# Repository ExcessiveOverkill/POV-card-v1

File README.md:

# Persistence of Vision Badge
Turn on then shake side to side to view the images or animations programmed into the badge.

## Specs:
- Requires 2x CR2032 batteries (badge is not rechargeable)
- Credit card sized: 2.1" x 3.3" (54mm x 84mm)
- 0.8mm PCB thickness, 4mm total thickness with components
- Black PCB soldermask
- 32 bright white leds
- ENIG (thin gold) plated

## Features:
- Image or animation display
- User programmable images/animations over USB-C
- User configurable modes set by tapping the badge
- 4-bit grayscale image support
- Many new display modes
- XYZ Accelerometer
- True power-off (batteries last when not in use)
- Auto power-off

# How to use:
## Turning On:
1. Press "ON" button on badge.
2. Badge will display power-on animation when first powered on.

Pressing the "ON" button once badge is already on will have no effect.

## Turning Off:
1. Do nothing
2. Badge will automatically power off after it is no longer being interacted with for around 20 seconds. It will also power off regardless of interaction after 5 minutes.

## Changing Mode:
1. Turn badge on
2. Tap top of badge downward 3 times quickly to enter the mode menue, it should display the current mode by turning on an LED. The distance the LED is from the bottom of the badge shows what mode it is in.
3. Tap top of badge downward to move LED down, Tap bottom of badge upward to move LED up
4. Wait 3 seconds for badge to enter new mode. You may shake the badge while in the mode menu to view what mode is selected. For SAVE MODE, LEVEL CAL, RESET and USB UPDATE, shaking is also the confirmation (see Mode Verification).
5. Done!

## USB Programming:
1. Turn badge on
2. Plug into a USB-A port on the computer, or into a USB-C to USB-A adapter or hub, using a USB-C to USB-A cable that carries data. A USB-C port on the computer will not work: the badge's connector has no CC pull-down resistors, so a USB-C host never enables the connection.
3. Badge will display slow pulsing to indicate USB connection.
4. Badge should show up as a USB storage device (flash drive).
5. Copy your BMP file to the badge
6. Done!
   
### BMP File Requirements:
- 1-bit or 4-bit grayscale
- 8, 16, or 32 pixels tall
- 128 or less pixels wide (per frame)
- Filename must end in "1" or "2" to indicate which slot you want to program
- For animations (multiple frames displayed in sequence), the filename must start with "SEQ"
- Animation frames must be separated by a 1 pixel wide column of alternating colors (0-1 for 1-bit, 0-15 for 4-bit). With the top pixel starting as 1 or 15 (white).
- File size must be less than 2KB

## How to get a good image
Image quality greatly depends on the shaking motion. Use mode 8: "IMAGE LINE TEST" to visualize your shake motion.
### Things to improve display quality
- Hold badge further away
- Smooth, uniform shaking. Slower and more consistent is better than fast and crazy.
- Shake left/right, not tilted or up/down
- Symmetrical movement, *not* like trying to shake ketchup out of a bottle.

## Modes
### 1. DISPLAY BOTH
Display both the pre-programmed image/animation shipped with the badge as well as all custom user-programmed images/animations.

### 2. DISPLAY CUSTOM
Display only the custom user-programmed images/animations.

### 3. LEVEL
Emulates a bubble level. Hold the badge edge against a vertical or horizontal surface. Use the "LEVEL CAL" mode to improve accuracy.

### 4. BALL SIM
LEDs display a "ball" that reacts to how you move and tilt the badge.

### 5. SAVE MODE
Save the last selected mode and automatically switch to it on the next power-on.
This function requires verification (see below).

### 6. LEVEL CAL
Calibrate the angles the badge uses for "LEVEL" mode. After entering this mode, hold the long badge still against a known horizontal surface until the LEDs all turn on. Then hold the short edge still against the surface until the "bubble" resets to center.
This function requires verification (see below).

### 7. RESET
Clears all user-programmed memory. Badge will power off after this mode is selected.
This function requires verification (see below).

### 8. IMAGE LINE TEST
Displays a diagonal line. Useful for practicing the correct shake technique to get the best display results.
The line should be perfectly straight and vertical when you shake the badge. Slight distortion is acceptable, but if it is very distorted, read the "How to get a good image" section.

## Firmware Update (DANGER)
### 9. USB Device Firmware Update
Allows the badge to be fully reprogrammed with a new binary file using STM32CubeProgrammer over the USB port. Selecting this mode arms the update instead of starting it: after the verification shake, the two end LEDs blink for one minute while the badge waits for a computer. Hold the ON button, then plug the badge into a USB-A port (see USB Programming). When the computer mounts the badge's drive, the badge switches into the bootloader: the drive disappears and the badge goes dark, and it stays dark until it is reprogrammed, so keep holding ON and run STM32CubeProgrammer with `-ob nBOOT0=1` added to reset the DFU bit; otherwise the badge stays stuck in DFU mode. If nothing connects within the minute, the badge powers off and nothing has changed. An ST-LINK can reprogram the badge at any time and does not need this mode.
User-memory will also be cleared.

## Mode Verification
Certain modes are protected by a verification step to prevent accidental triggering.
These modes will display a bar at the bottom the image that slowly shrinks while you shake the badge.
You must continuously shake the badge until the bar is gone to enable the selected mode.
USB UPDATE additionally waits for a computer to connect before it acts (see Firmware Update).

# Warnings/Notices:
- The badge is a bare PCB, it is very susceptible water and metallic objects and dust. Keep clean and do not put in contact with loose conductive objects
- Badge is not rechargeable, the USB-C port does not supply power to the badge circuitry.
- This "Development Edition" is the first publicly available version. There may be unforeseen issues with hardware or software that affect functionality. However we will do our best to verify all use cases and resolve potential issues before you receive your badge.
- Persistence-of-vision effects are notoriously hard to film. Cameras will not capture the effect well without a very slow shutter speed.
- Attached lanyards or clips that rattle against the badge will affect the accelerometer reading and can make the image distorted.

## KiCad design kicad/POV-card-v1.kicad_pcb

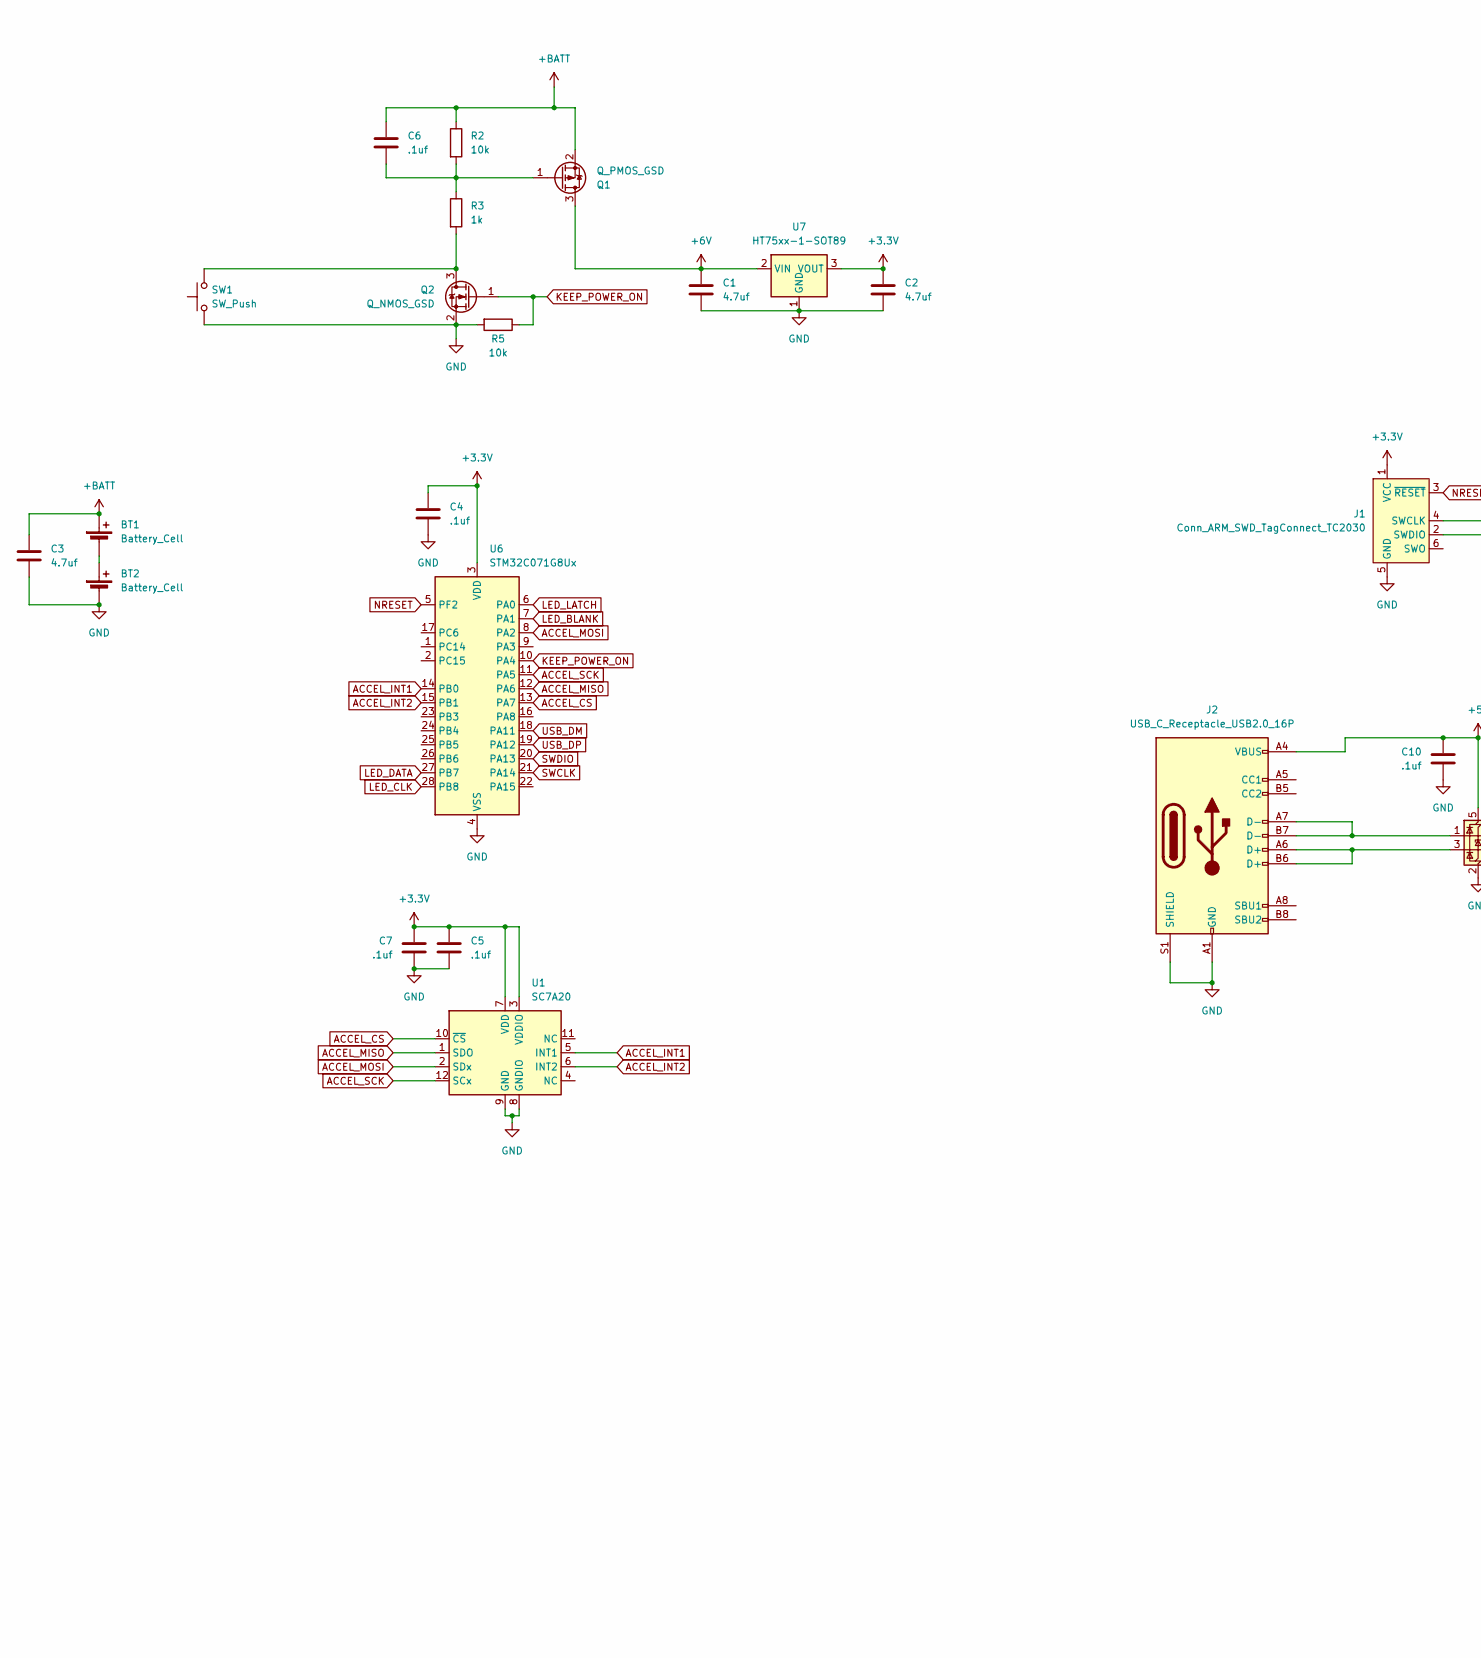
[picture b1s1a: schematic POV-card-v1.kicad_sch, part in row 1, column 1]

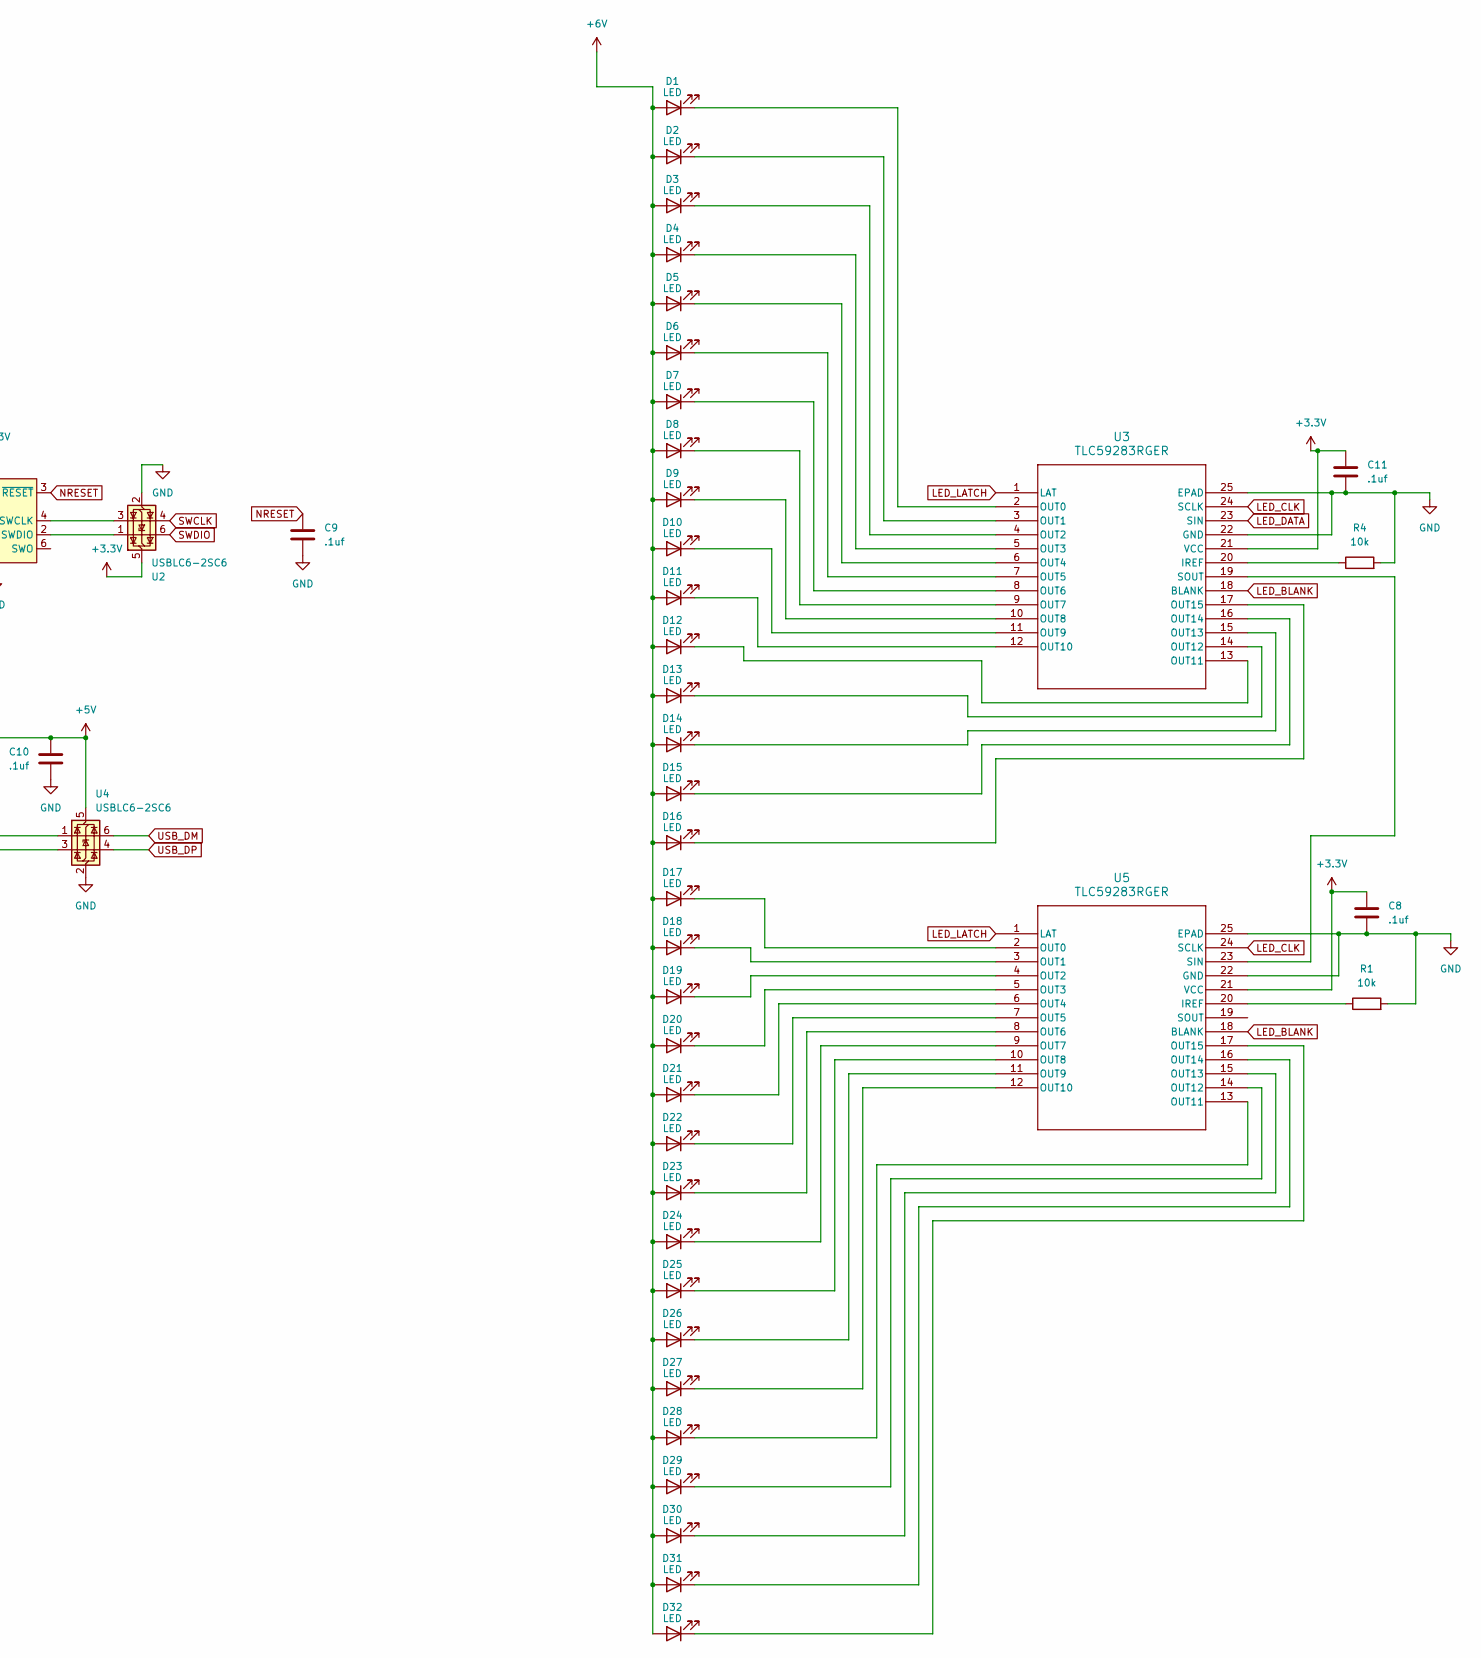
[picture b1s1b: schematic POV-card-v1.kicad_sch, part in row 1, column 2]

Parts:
BT1, BT2: Battery_Cell; cr2032; Manufacturer part number MY-2032-30-R; LCSC# C19184123
C1, C2, C3: 4.7uf; C_0402_1005Metric; Manufacturer part number CL05A475MP5NRNC; LCSC# C23733
C4, C5, C6, C7, C8, C9, C10, C11: .1uf; C_0402_1005Metric; Manufacturer part number CL05B104KO5NNNC; LCSC# C1525
D1, D2, D3, D4, D5, D6, D7, D8, D9, D10, D11, D12, D13, D14, D15, D16, D17, D18, D19, D20, D21, D22, D23, D24, D25, D26, D27, D28, D29, D30, D31, D32: LED; LED_0603_1608Metric; Manufacturer part number KT-0603W; LCSC# C2290
J1: Conn_ARM_SWD_TagConnect_TC2030; Tag-Connect_TC2030-IDC-FP_2x03_P1.27mm_Vertical
J2: USB_C_Receptacle_USB2.0_16P; USB_C_Receptacle_G-Switch_GT-USB-7010ASV; Manufacturer part number GT-USB-7010ASV; LCSC# C2988369
Q1: Q_PMOS_GSD; SOT-23; Manufacturer part number AO3401A; LCSC# C15127
Q2: Q_NMOS_GSD; SOT-23; Manufacturer part number 2N7002; LCSC# C8545
R1, R2, R4, R5: 10k; R_0402_1005Metric; Manufacturer part number 0402WGF1002TCE; LCSC# C25744
R3: 1k; R_0402_1005Metric; Manufacturer part number 0402WGF1001TCE; LCSC# C11702
SW1: SW_Push; SW_Push_1P1T_XKB_TS-1187A; Manufacturer part number TS-1187A-B-A-B; LCSC# C318884
U1: SC7A20; LGA-12_2x2mm_P0.5mm; Manufacturer part number SC7A20HTR; LCSC# C19274408
U2, U4: USBLC6-2SC6; SOT-23-6; Manufacturer part number USBLC6-2SC6; LCSC# C2687116
U3, U5: TLC59283RGER; RGE24_2P1X2P1_TEX; Manufacturer part number TLC59283RGER; LCSC# C485815
U6: STM32C071G8Ux; QFN-28_4x4mm_P0.5mm; Manufacturer part number STM32C071G8U6; LCSC# C44521811
U7: HT75xx-1-SOT89; SOT-89-3; Manufacturer part number HT7533-1; LCSC# t # C14289

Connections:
+3.3V: C2.1, C4.1, C5.1, C7.1, C8.1, C11.1, J1.1 (VCC), U1.3 (VDDIO), U1.7 (VDD), U2.5 (VBUS), U3.21 (VCC), U5.21 (VCC), U6.3 (VDD), U7.3 (VOUT)
+5V: C10.1, J2.A4 (VBUS), J2.A9 (VBUS), J2.B4 (VBUS), J2.B9 (VBUS), U4.5 (VBUS)
+6V: C1.1, D1.2 (A), D2.2 (A), D3.2 (A), D4.2 (A), D5.2 (A), D6.2 (A), D7.2 (A), D8.2 (A), D9.2 (A), D10.2 (A), D11.2 (A), D12.2 (A), D13.2 (A), D14.2 (A), D15.2 (A), D16.2 (A), D17.2 (A), D18.2 (A), D19.2 (A), D20.2 (A), D21.2 (A), D22.2 (A), D23.2 (A), D24.2 (A), D25.2 (A), D26.2 (A), D27.2 (A), D28.2 (A), D29.2 (A), D30.2 (A), D31.2 (A), D32.2 (A), Q1.3 (D), U7.2 (VIN)
+BATT: BT1.1 (+), C3.1, C6.1, Q1.2 (S), R2.1
ACCEL_CS: U1.10 (~CS), U6.13 (PA7)
ACCEL_INT1: U1.5 (INT1), U6.14 (PB0)
ACCEL_INT2: U1.6 (INT2), U6.15 (PB1)
ACCEL_MISO: U1.1 (SDO), U6.12 (PA6)
ACCEL_MOSI: U1.2 (SDx), U6.8 (PA2)
ACCEL_SCK: U1.12 (SCx), U6.11 (PA5)
GND: BT2.2 (-), C1.2, C2.2, C3.2, C4.2, C5.2, C7.2, C8.2, C9.2, C10.2, C11.2, J1.5 (GND), J2.A1 (GND), J2.A12 (GND), J2.B1 (GND), J2.B12 (GND), J2.S1 (SHIELD), Q2.2 (S), R1.2, R4.2, R5.2, SW1.1, U1.8 (GNDIO), U1.9 (GND), U2.2 (GND), U3.22 (GND), U3.25 (EPAD), U4.2 (GND), U5.22 (GND), U5.25 (EPAD), U6.4 (VSS), U7.1 (GND)
KEEP_POWER_ON: Q2.1 (G), R5.1, U6.10 (PA4)
LED_BLANK: U3.18 (BLANK), U5.18 (BLANK), U6.7 (PA1)
LED_CLK: U3.24 (SCLK), U5.24 (SCLK), U6.28 (PB8)
LED_DATA: U3.23 (SIN), U6.27 (PB7)
LED_LATCH: U3.1 (LAT), U5.1 (LAT), U6.6 (PA0)
NRESET: C9.1, J1.3 (~RESET), U6.5 (PF2)
unnamed: BT1.2 (-), BT2.1 (+)
unnamed: D1.1 (K), U3.2 (OUT0)
unnamed: D2.1 (K), U3.3 (OUT1)
unnamed: D3.1 (K), U3.4 (OUT2)
unnamed: D4.1 (K), U3.5 (OUT3)
unnamed: D5.1 (K), U3.6 (OUT4)
unnamed: D6.1 (K), U3.7 (OUT5)
unnamed: D7.1 (K), U3.8 (OUT6)
unnamed: D8.1 (K), U3.9 (OUT7)
unnamed: D9.1 (K), U3.10 (OUT8)
unnamed: D10.1 (K), U3.11 (OUT9)
unnamed: D11.1 (K), U3.12 (OUT10)
unnamed: D12.1 (K), U3.13 (OUT11)
unnamed: D13.1 (K), U3.14 (OUT12)
unnamed: D14.1 (K), U3.15 (OUT13)
unnamed: D15.1 (K), U3.16 (OUT14)
unnamed: D16.1 (K), U3.17 (OUT15)
unnamed: D17.1 (K), U5.2 (OUT0)
unnamed: D18.1 (K), U5.3 (OUT1)
unnamed: D19.1 (K), U5.4 (OUT2)
unnamed: D20.1 (K), U5.5 (OUT3)
unnamed: D21.1 (K), U5.6 (OUT4)
unnamed: D22.1 (K), U5.7 (OUT5)
unnamed: D23.1 (K), U5.8 (OUT6)
unnamed: D24.1 (K), U5.9 (OUT7)
unnamed: D25.1 (K), U5.10 (OUT8)
unnamed: D26.1 (K), U5.11 (OUT9)
unnamed: D27.1 (K), U5.12 (OUT10)
unnamed: D28.1 (K), U5.13 (OUT11)
unnamed: D29.1 (K), U5.14 (OUT12)
unnamed: D30.1 (K), U5.15 (OUT13)
unnamed: D31.1 (K), U5.16 (OUT14)
unnamed: D32.1 (K), U5.17 (OUT15)
unnamed: J1.4 (SWCLK), U2.3 (I/O2)
unnamed: J1.2 (SWDIO), U2.1 (I/O1)
unnamed: J2.A6 (D+), J2.B6 (D+), U4.3 (I/O2)
unnamed: J2.A7 (D-), J2.B7 (D-), U4.1 (I/O1)
unnamed: C6.2, Q1.1 (G), R2.2, R3.1
unnamed: Q2.3 (D), R3.2, SW1.2
unnamed: R4.1, U3.20 (IREF)
unnamed: U3.19 (SOUT), U5.23 (SIN)
unnamed: R1.1, U5.20 (IREF)
SWCLK: U2.4 (I/O2), U6.21 (PA14)
SWDIO: U2.6 (I/O1), U6.20 (PA13)
USB_DM: U4.6 (I/O1), U6.18 (PA11)
USB_DP: U4.4 (I/O2), U6.19 (PA12)

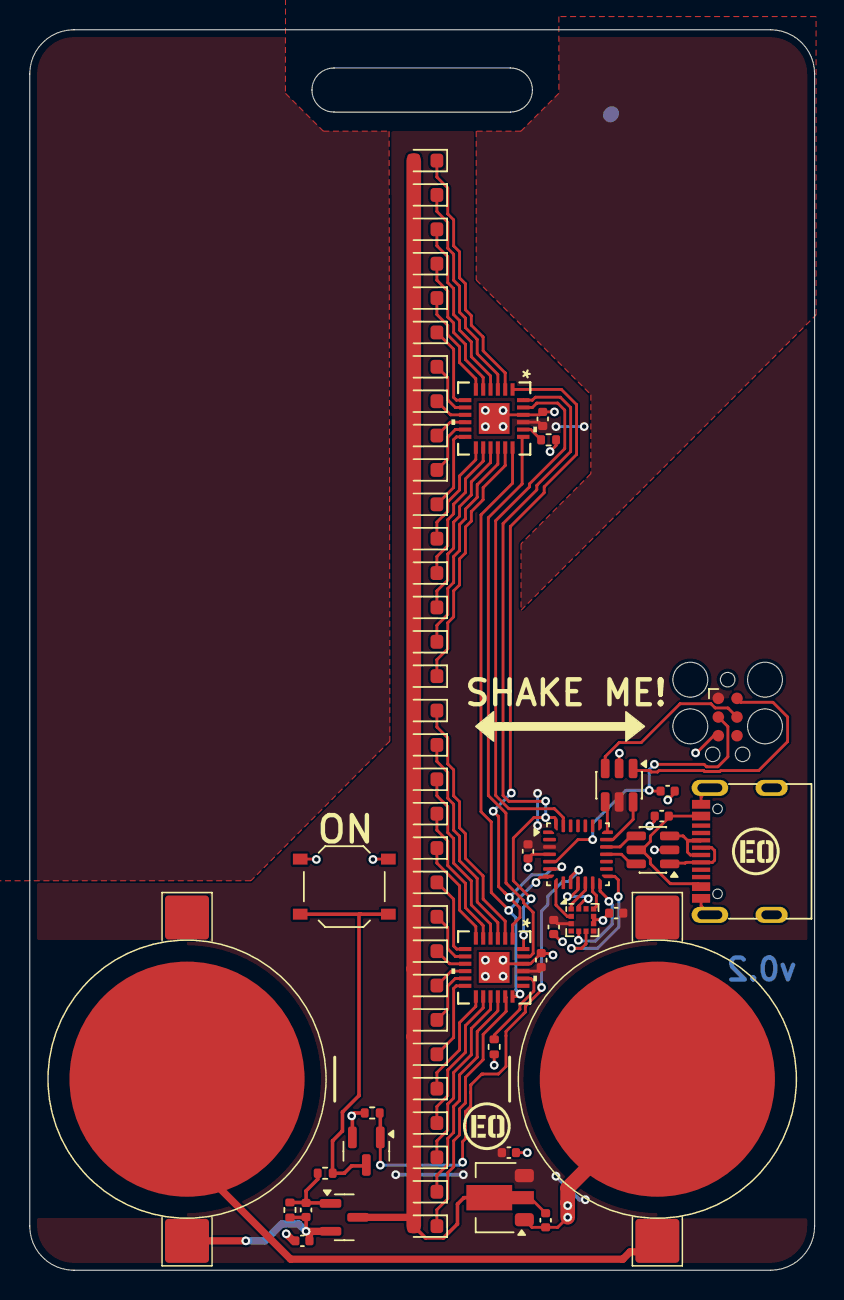
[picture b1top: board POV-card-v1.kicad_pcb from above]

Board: 2 copper layers, 53.4 x 84.4 mm, 62 parts (0 on the bottom side), 63 nets.

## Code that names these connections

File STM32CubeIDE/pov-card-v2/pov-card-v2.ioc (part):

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Mcu.Name=STM32C071G8Ux
Mcu.Package=UFQFPN28_GP
Mcu.UserName=STM32C071G8Ux
PA0.GPIOParameters=GPIO_Speed,GPIO_Label
PA0.GPIO_Label=LED_LATCH
PA0.GPIO_Speed=GPIO_SPEED_FREQ_VERY_HIGH
PA0.Signal=S_TIM1_CH1
PA1.GPIOParameters=GPIO_Speed,GPIO_Label
PA1.GPIO_Label=LED_BLANK
PA1.GPIO_Speed=GPIO_SPEED_FREQ_VERY_HIGH
PA1.Signal=S_TIM1_CH2
PA11\ [PA9].Mode=Device
PA11\ [PA9].Signal=USB_DM
PA12\ [PA10].Mode=Device
PA12\ [PA10].Signal=USB_DP
PA13.Mode=Serial_Wire
PA13.Signal=DEBUG_SWDIO
PA14-BOOT0.Mode=Serial_Wire
PA14-BOOT0.Signal=DEBUG_SWCLK
PA2.GPIOParameters=GPIO_Speed,GPIO_Label
PA2.GPIO_Label=ACCEL_MOSI
PA2.GPIO_Speed=GPIO_SPEED_FREQ_HIGH
PA2.Mode=Full_Duplex_Master
PA2.Signal=SPI1_MOSI
PA3.GPIOParameters=GPIO_Speed,GPIO_Label,GPIO_ModeDefaultEXTI
PA3.GPIO_Label=DMA_TRIG
PA3.GPIO_ModeDefaultEXTI=GPIO_MODE_EVT_RISING
PA3.GPIO_Speed=GPIO_SPEED_FREQ_VERY_HIGH
PA3.Signal=SharedStack_PA3
PA3.Stacked=true
PA4.GPIOParameters=GPIO_Label
PA4.GPIO_Label=KEEP_POWER_ON
PA4.Signal=GPIO_Output
PA5.GPIOParameters=GPIO_Speed,GPIO_Label
PA5.GPIO_Label=ACCEL_SCK
PA5.GPIO_Speed=GPIO_SPEED_FREQ_HIGH
PA5.Mode=Full_Duplex_Master
PA5.Signal=SPI1_SCK
PA6.GPIOParameters=GPIO_Speed,GPIO_Label
PA6.GPIO_Label=ACCEL_MISO
PA6.GPIO_Speed=GPIO_SPEED_FREQ_HIGH
PA6.Mode=Full_Duplex_Master
PA6.Signal=SPI1_MISO
PA7.GPIOParameters=GPIO_Speed,PinState,GPIO_Label
PA7.GPIO_Label=ACCEL_CS
PA7.GPIO_Speed=GPIO_SPEED_FREQ_HIGH
PA7.PinState=GPIO_PIN_SET
PA7.Signal=GPIO_Output
PB0.GPIOParameters=GPIO_Label
PB0.GPIO_Label=ACCEL_INT1
PB0.Signal=GPXTI0
PB1.GPIOParameters=GPIO_Label
PB1.GPIO_Label=ACCEL_INT2
PB1.Signal=GPIO_Input
PB6.Signal=GPIO_Output
PB7.GPIOParameters=GPIO_Speed,GPIO_Label
PB7.GPIO_Label=LED_DATA
PB7.GPIO_Speed=GPIO_SPEED_FREQ_VERY_HIGH
PB7.Mode=TX_Only_Simplex_Unidirect_Master
PB7.Signal=SPI2_MOSI
PB8.GPIOParameters=GPIO_Speed,GPIO_Label
PB8.GPIO_Label=LED_CLK
PB8.GPIO_Speed=GPIO_SPEED_FREQ_VERY_HIGH
PB8.Mode=TX_Only_Simplex_Unidirect_Master
PB8.Signal=SPI2_SCK
RCC.HSE_VALUE=8000000
RCC.SYSCLKFreq_VALUE=48000000
RCC.SYSCLKSource=RCC_SYSCLKSOURCE_HSIUSB48
board=custom

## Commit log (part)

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2026-06-09 initial
